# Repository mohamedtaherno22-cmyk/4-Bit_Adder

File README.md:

# 4-Bit_Adder
A 4-bit adder built entirely from discrete transistors and resistors. The project explores digital logic at the hardware level, combining 30 NOR Gates and 1 AND gate to form 3 full adders and 1 half adder. Everything is assembled onto a custom 8cm x 7cm PCB. You can extend the circuit beyond 4 bits by adding more full-adders, allowing it to handle higher binary addition. Each additional stage uses the carry-out from the previous stage as its carry-in (Ci).

## Features

- **4-Bit Binary Adder:** Adds two 4-bit binary numbers using a transistor-based logic circuit.
- **LED Output Indicators:** LEDs display the resulting binary sum and the carry-out, for an easy-to-read output.
- **Switch-Controlled Inputs:** Allows users to manually set the binary inputs and test different addition combinations.
- **Compact PCB Design:** The entire circuit is assembled onto a double-layered 8 × 7.5 cm PCB.

## Hardware

- **31 NPN Transistors:** make up the logic gates that make up the adder.
- **Resistors:** Includes 5 × 220Ω (for LEDs ouput), 60 × 10kΩ (Handle the transistor input), and 30 × 4.7kΩ pull-up resistors.
- **5 LEDs:** Used to display the binary output bits and the final carry.
- **8 Switches:** Used to manually set the input bits for the two binary numbers.
- **PCB (can be replaced by breadboards)**

## Schematics
**AND_Gate & NOR_GATE**

**Half-Adder (2-Bit Adder)**

**Full-Adder (3-Bit Adder)**

**Schematic**

## PCB

## 3D Model

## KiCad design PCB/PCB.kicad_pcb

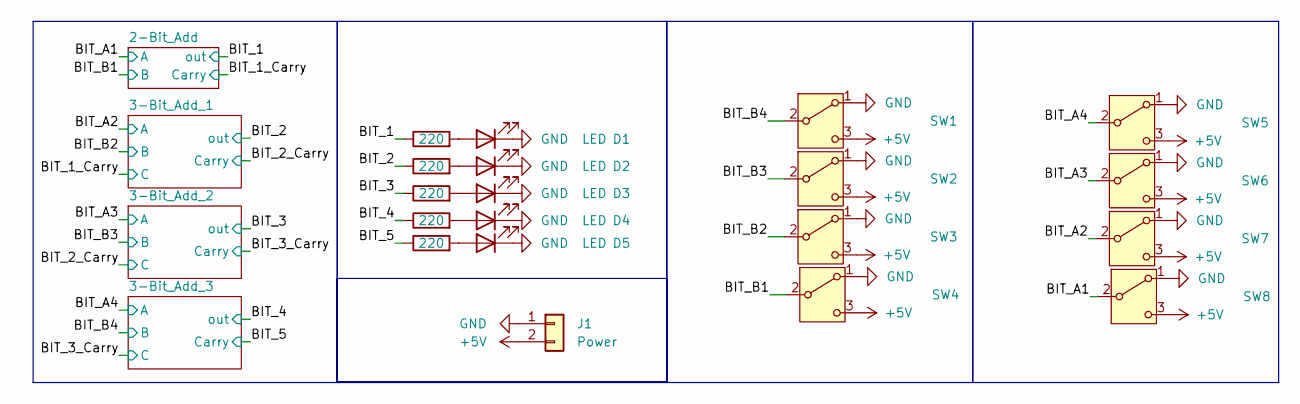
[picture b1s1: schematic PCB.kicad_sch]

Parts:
D1, D2, D3, D4, D5: LED; LED_D5.0mm
J1: Power; PinHeader_2x01_P2.54mm_Vertical
R1, R2, R3, R4, R5: 220; R_Axial_DIN0207_L6.3mm_D2.5mm_P10.16mm_Horizontal
SW1, SW2, SW3, SW4, SW5, SW6, SW7, SW8: SW_SPDT; PinHeader_1x03_P2.54mm_Vertical

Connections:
/BIT_1: R1.1; also elsewhere on the board
/BIT_2: R2.1; also elsewhere on the board
/BIT_3: R3.1; also elsewhere on the board
/BIT_4: R4.1; also elsewhere on the board
/BIT_5: R5.1; also elsewhere on the board
GND: D1.1 (K), D2.1 (K), D3.1 (K), D4.1 (K), D5.1 (K), J1.1, SW1.1 (A), SW2.1 (A), SW3.1 (A), SW4.1 (A), SW5.1 (A), SW6.1 (A), SW7.1 (A), SW8.1 (A); also elsewhere on the board
unnamed: D1.2 (A), R1.2
unnamed: D2.2 (A), R2.2
unnamed: D3.2 (A), R3.2
unnamed: D4.2 (A), R4.2
unnamed: D5.2 (A), R5.2
unnamed: J1.2, SW1.3 (C), SW2.3 (C), SW3.3 (C), SW4.3 (C), SW5.3 (C), SW6.3 (C), SW7.3 (C), SW8.3 (C)

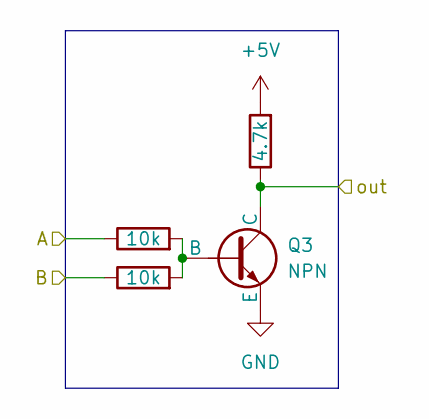
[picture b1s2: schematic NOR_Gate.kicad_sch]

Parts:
Q3: NPN; TO-92_Inline
R9, R10: 10k; R_Axial_DIN0207_L6.3mm_D2.5mm_P10.16mm_Horizontal
R11: 4.7k; R_Axial_DIN0207_L6.3mm_D2.5mm_P10.16mm_Horizontal

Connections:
+5V: R11.2; also elsewhere on the board
/2-Bit_Add/NOR_Gate_1/out: Q3.1 (C), R11.1; also elsewhere on the board
/BIT_A1: R9.1; also elsewhere on the board
/BIT_B1: R10.1; also elsewhere on the board
GND: Q3.3 (E); also elsewhere on the board
unnamed: Q3.2 (B), R9.2, R10.2

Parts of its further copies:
Q4, Q5, Q6, Q7, Q8, Q9, Q10, Q11, Q12, Q13, Q14, Q15, Q16, Q17, Q18, Q19, Q20, Q21, Q22, Q23, Q24, Q25, Q26, Q27, Q28, Q29, Q30, Q31: NPN; TO-92_Inline
R12, R13, R15, R16, R18, R19, R21, R22, R24, R25, R27, R28, R30, R31, R33, R34, R36, R37, R39, R40, R42, R43, R45, R46, R48, R49, R51, R52, R54, R55, R57, R58, R60, R61, R63, R64, R66, R67, R69, R70, R72, R73, R75, R76, R78, R79, R81, R82, R84, R85, R87, R88, R90, R91, R93, R94: 10k; R_Axial_DIN0207_L6.3mm_D2.5mm_P10.16mm_Horizontal
R14, R17, R20, R23, R26, R29, R32, R35, R38, R41, R44, R47, R50, R53, R56, R59, R62, R65, R68, R71, R74, R77, R80, R83, R86, R89, R92, R95: 4.7k; R_Axial_DIN0207_L6.3mm_D2.5mm_P10.16mm_Horizontal

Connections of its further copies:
+5V: R14.2, R17.2, R20.2, R23.2, R26.2, R29.2, R32.2, R35.2, R38.2, R41.2, R44.2, R47.2, R50.2, R53.2, R56.2, R59.2, R62.2, R65.2, R68.2, R71.2, R74.2, R77.2, R80.2, R83.2, R86.2, R89.2, R92.2, R95.2; also elsewhere on the board
/2-Bit_Add/NOR_Gate_1/out: R12.1; also elsewhere on the board
/3-Bit_Add_1/NOR_Gate_3/out: Q24.1 (C), R70.1, R74.1, R75.1, R85.1
/3-Bit_Add_1/NOR_Gate_4/out: Q23.1 (C), R71.1, R78.1
/3-Bit_Add_1/NOR_Gate_5/out: Q25.1 (C), R77.1, R79.1
/3-Bit_Add_1/NOR_Gate_6/out: Q26.1 (C), R80.1, R81.1, R87.1
/3-Bit_Add_1/NOR_Gate_10/B: Q27.1 (C), R83.1, R84.1, R88.1, R91.1
/3-Bit_Add_1/NOR_Gate_10/out: Q30.1 (C), R92.1, R94.1
/3-Bit_Add_1/NOR_Gate_11/A: Q29.1 (C), R89.1, R93.1
/3-Bit_Add_2/NOR_Gate_3/out: Q6.1 (C), R20.1, R22.1, R24.1, R40.1
/3-Bit_Add_2/NOR_Gate_4/out: Q7.1 (C), R23.1, R33.1
/3-Bit_Add_2/NOR_Gate_5/out: Q8.1 (C), R26.1, R34.1
/3-Bit_Add_2/NOR_Gate_6/out: Q11.1 (C), R27.1, R35.1, R36.1
/3-Bit_Add_2/NOR_Gate_10/B: Q12.1 (C), R28.1, R31.1, R38.1, R39.1
/3-Bit_Add_2/NOR_Gate_10/out: Q10.1 (C), R16.1, R32.1
/3-Bit_Add_2/NOR_Gate_11/A: Q9.1 (C), R15.1, R29.1
/3-Bit_Add_3/NOR_Gate_3/out: Q15.1 (C), R47.1, R49.1, R51.1, R67.1
/3-Bit_Add_3/NOR_Gate_4/out: Q16.1 (C), R50.1, R60.1
/3-Bit_Add_3/NOR_Gate_5/out: Q17.1 (C), R53.1, R61.1
/3-Bit_Add_3/NOR_Gate_6/out: Q20.1 (C), R54.1, R62.1, R63.1
/3-Bit_Add_3/NOR_Gate_10/B: Q21.1 (C), R55.1, R58.1, R65.1, R66.1
/3-Bit_Add_3/NOR_Gate_10/out: Q19.1 (C), R43.1, R59.1
/3-Bit_Add_3/NOR_Gate_11/A: Q18.1 (C), R42.1, R56.1
/BIT_1: Q4.1 (C), R14.1; also elsewhere on the board
/BIT_1_Carry: R13.1, R82.1, R90.1; also elsewhere on the board
/BIT_2: Q31.1 (C), R95.1; also elsewhere on the board
/BIT_2_Carry: Q28.1 (C), R30.1, R37.1, R86.1
/BIT_3: Q5.1 (C), R17.1; also elsewhere on the board
/BIT_3_Carry: Q13.1 (C), R41.1, R57.1, R64.1
/BIT_4: Q14.1 (C), R44.1; also elsewhere on the board
/BIT_5: Q22.1 (C), R68.1; also elsewhere on the board
/BIT_A2: R69.1, R72.1; also elsewhere on the board
/BIT_A3: R18.1, R21.1; also elsewhere on the board
/BIT_A4: R45.1, R48.1; also elsewhere on the board
/BIT_B2: R73.1, R76.1; also elsewhere on the board
/BIT_B3: R19.1, R25.1; also elsewhere on the board
/BIT_B4: R46.1, R52.1; also elsewhere on the board
GND: Q4.3 (E), Q5.3 (E), Q6.3 (E), Q7.3 (E), Q8.3 (E), Q9.3 (E), Q10.3 (E), Q11.3 (E), Q12.3 (E), Q13.3 (E), Q14.3 (E), Q15.3 (E), Q16.3 (E), Q17.3 (E), Q18.3 (E), Q19.3 (E), Q20.3 (E), Q21.3 (E), Q22.3 (E), Q23.3 (E), Q24.3 (E), Q25.3 (E), Q26.3 (E), Q27.3 (E), Q28.3 (E), Q29.3 (E), Q30.3 (E), Q31.3 (E); also elsewhere on the board
unnamed: Q4.2 (B), R12.2, R13.2
unnamed: Q5.2 (B), R15.2, R16.2
unnamed: Q6.2 (B), R18.2, R19.2
unnamed: Q7.2 (B), R21.2, R22.2
unnamed: Q8.2 (B), R24.2, R25.2
unnamed: Q9.2 (B), R27.2, R28.2
unnamed: Q10.2 (B), R30.2, R31.2
unnamed: Q11.2 (B), R33.2, R34.2
unnamed: Q12.2 (B), R36.2, R37.2
unnamed: Q13.2 (B), R39.2, R40.2
unnamed: Q14.2 (B), R42.2, R43.2
unnamed: Q15.2 (B), R45.2, R46.2
unnamed: Q16.2 (B), R48.2, R49.2
unnamed: Q17.2 (B), R51.2, R52.2
unnamed: Q18.2 (B), R54.2, R55.2
unnamed: Q19.2 (B), R57.2, R58.2
unnamed: Q20.2 (B), R60.2, R61.2
unnamed: Q21.2 (B), R63.2, R64.2
unnamed: Q22.2 (B), R66.2, R67.2
unnamed: Q23.2 (B), R69.2, R70.2
unnamed: Q24.2 (B), R72.2, R73.2
unnamed: Q25.2 (B), R75.2, R76.2
unnamed: Q26.2 (B), R78.2, R79.2
unnamed: Q27.2 (B), R81.2, R82.2
unnamed: Q28.2 (B), R84.2, R85.2
unnamed: Q29.2 (B), R87.2, R88.2
unnamed: Q30.2 (B), R90.2, R91.2
unnamed: Q31.2 (B), R93.2, R94.2

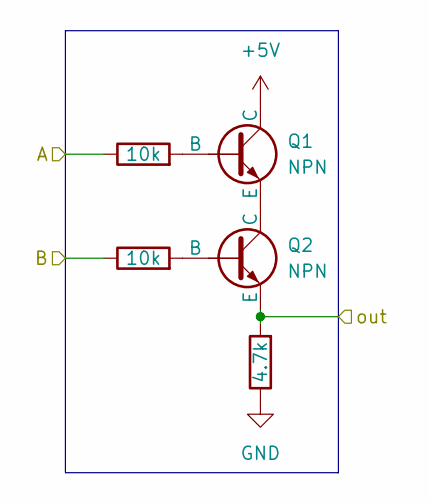
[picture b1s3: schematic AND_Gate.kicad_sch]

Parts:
Q1, Q2: NPN; TO-92_Inline
R6, R7: 10k; R_Axial_DIN0207_L6.3mm_D2.5mm_P10.16mm_Horizontal
R8: 4.7k; R_Axial_DIN0207_L6.3mm_D2.5mm_P10.16mm_Horizontal

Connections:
+5V: Q1.1 (C); also elsewhere on the board
/BIT_1_Carry: Q2.3 (E), R8.2; also elsewhere on the board
/BIT_A1: R6.1; also elsewhere on the board
/BIT_B1: R7.1; also elsewhere on the board
GND: R8.1; also elsewhere on the board
unnamed: Q1.2 (B), R6.2
unnamed: Q1.3 (E), Q2.1 (C)
unnamed: Q2.2 (B), R7.2

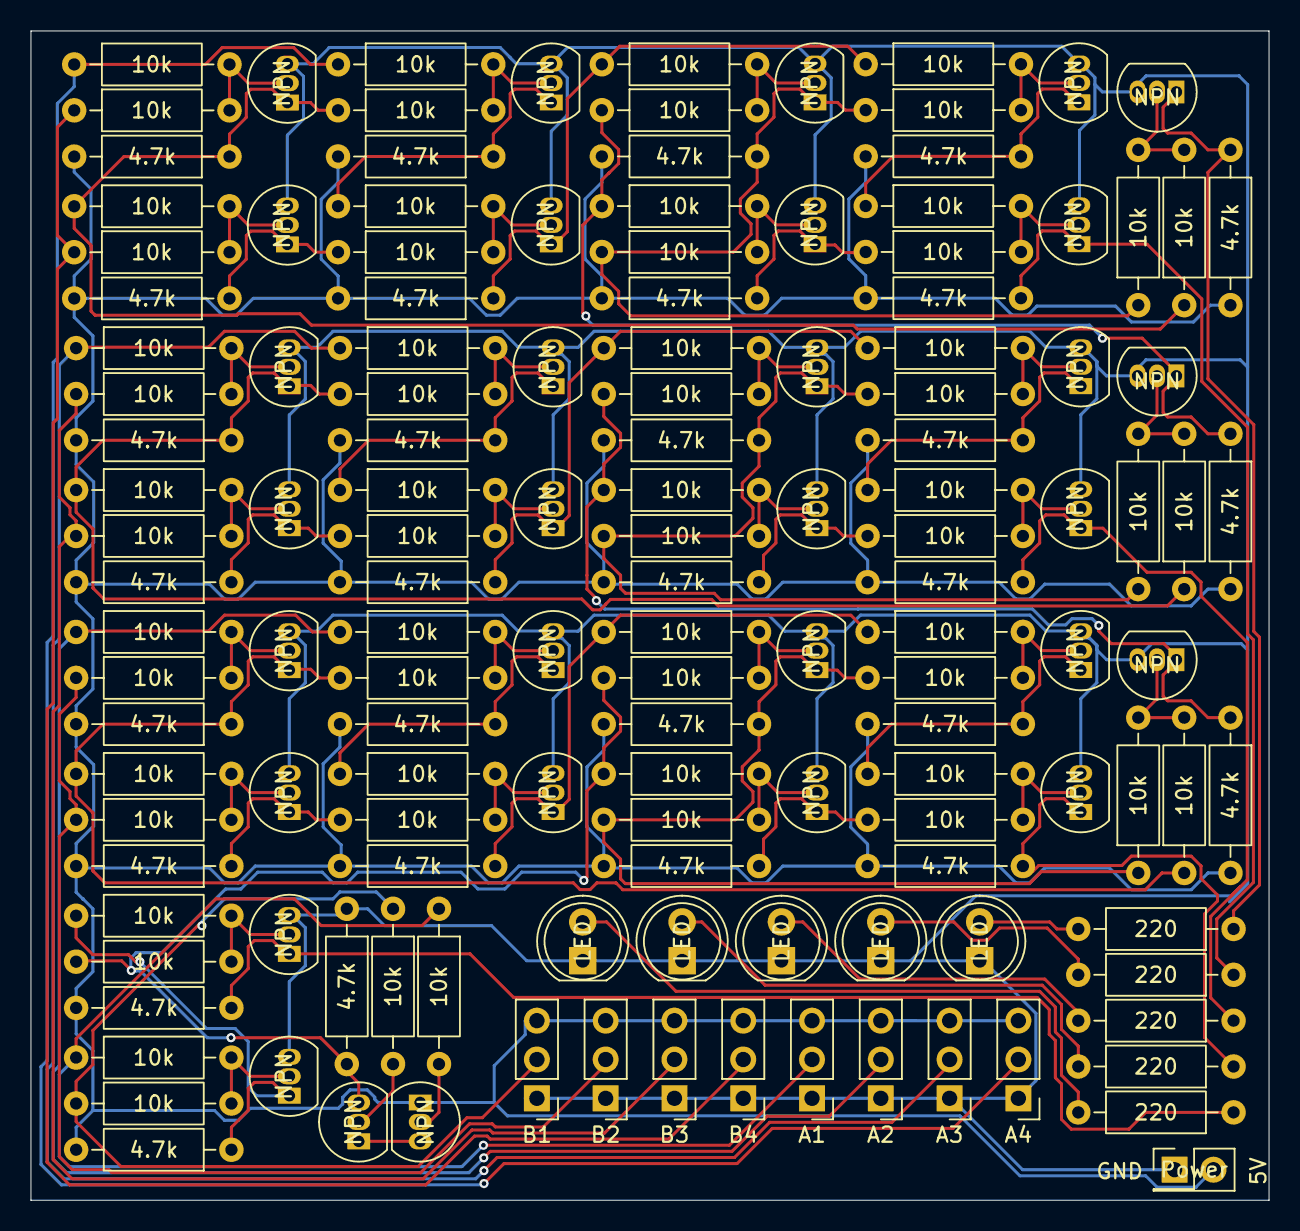
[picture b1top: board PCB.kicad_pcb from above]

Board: 2 copper layers, 81.0 x 76.5 mm, 140 parts (0 on the bottom side), 77 nets.

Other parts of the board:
A1, A2, A3, A4: SW_SPDT; PinHeader_1x03_P2.54mm_Vertical
B1, B2, B3, B4: SW_SPDT; PinHeader_1x03_P2.54mm_Vertical
GND: Power; PinHeader_2x01_P2.54mm_Vertical

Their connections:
+5V: A1.3 (C), A2.3 (C), A3.3 (C), A4.3 (C), B1.3 (C), B2.3 (C), B3.3 (C), B4.3 (C), GND.2; also elsewhere on the board
/BIT_A1: A1.2 (B); also elsewhere on the board
/BIT_A2: A2.2 (B); also elsewhere on the board
/BIT_A3: A3.2 (B); also elsewhere on the board
/BIT_A4: A4.2 (B); also elsewhere on the board
/BIT_B1: B1.2 (B); also elsewhere on the board
/BIT_B2: B2.2 (B); also elsewhere on the board
/BIT_B3: B3.2 (B); also elsewhere on the board
/BIT_B4: B4.2 (B); also elsewhere on the board
GND: A1.1 (A), A2.1 (A), A3.1 (A), A4.1 (A), B1.1 (A), B2.1 (A), B3.1 (A), B4.1 (A), GND.1; also elsewhere on the board

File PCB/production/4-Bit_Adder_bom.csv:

Designator,Footprint,Quantity,Value,LCSC Part #
"A1, A2, A3, A4, B1, B2, B3, B4",PinHeader_1x03_P2.54mm_Vertical,8,SW_SPDT,
"D1, D2, D3, D4, D5",LED_D5.0mm,5,LED,
GND,PinHeader_2x01_P2.54mm_Vertical,1,Power,
"Q1, Q10, Q11, Q12, Q13, Q14, Q15, Q16, Q17, Q18, Q19, Q2, Q20, Q21, Q22, Q23, Q24, Q25, Q26, Q27, Q28, Q29, Q3, Q30, Q31, Q4, Q5, Q6, Q7, Q8, Q9",TO-92_Inline,31,NPN,
"R1, R2, R3, R4, R5",R_Axial_DIN0207_L6.3mm_D2.5mm_P10.16mm_Horizontal,5,220,
"R10, R12, R13, R15, R16, R18, R19, R21, R22, R24, R25, R27, R28, R30, R31, R33, R34, R36, R37, R39, R40, R42, R43, R45, R46, R48, R49, R51, R52, R54, R55, R57, R58, R6, R60, R61, R63, R64, R66, R67, R69, R7, R70, R72, R73, R75, R76, R78, R79, R81, R82, R84, R85, R87, R88, R9, R90, R91, R93, R94",R_Axial_DIN0207_L6.3mm_D2.5mm_P10.16mm_Horizontal,60,10k,
"R11, R14, R17, R20, R23, R26, R29, R32, R35, R38, R41, R44, R47, R50, R53, R56, R59, R62, R65, R68, R71, R74, R77, R8, R80, R83, R86, R89, R92, R95",R_Axial_DIN0207_L6.3mm_D2.5mm_P10.16mm_Horizontal,30,4.7k,
